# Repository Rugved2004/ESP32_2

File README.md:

# ESP32_2 - KiCad PCB Project

A custom ESP32-based PCB design created with KiCad 8.x.

## Overview

This repository contains the complete KiCad project files for an ESP32 development board. The design includes schematic capture, PCB layout, 3D models, and custom footprints/libraries.

## Project Structure

```
ESP32_2/
├── ESP32_2.kicad_pro      # Project configuration
├── ESP32_2.kicad_sch      # Schematic file
├── ESP32_2.kicad_pcb      # PCB layout file
├── ESP32_2.pdf            # PCB fabrication drawing
├── LIB/                   # Custom symbol libraries
├── Footprint/             # Custom footprint libraries
├── 3D_Modelss/            # 3D STEP models for components
├── ESP32_2-backups/       # Automatic KiCad backups
└── imgs/                  # Project images/screenshots
```

## Features

- **ESP32-WROOM-32** module integration
- Custom power management circuitry
- USB-C interface for programming and power
- GPIO breakout headers
- Custom footprint libraries for specific components
- 3D models for mechanical verification

## Getting Started

### Prerequisites

- [KiCad 8.0+](https://www.kicad.org/download/)

### Opening the Project

1. Clone this repository
2. Open `ESP32_2.kicad_pro` in KiCad
3. The schematic and PCB editors will be available

## Manufacturing

### PCB Fabrication

Gerber files can be generated from the PCB editor:
1. Open `ESP32_2.kicad_pcb`
2. File → Fabrication Outputs → Gerbers (.gbr)
3. Use the default settings for most fabs

### Bill of Materials (BOM)

Generate BOM from the schematic editor:
1. Open `ESP32_2.kicad_sch`
2. Tools → Generate Bill of Materials

## Custom Libraries

This project uses custom libraries located in:
- `LIB/` - Schematic symbols
- `Footprint/` - PCB footprints

These are referenced in the project configuration and should be available when opening the project.

## License

This project is open source. Feel free to use, modify, and distribute.

## Author

**Rugved Bhalekar**
- GitHub: [@Rugved2004](https://github.com/Rugved2004)
- Email: rugvedbhalekar2004@gmail.com

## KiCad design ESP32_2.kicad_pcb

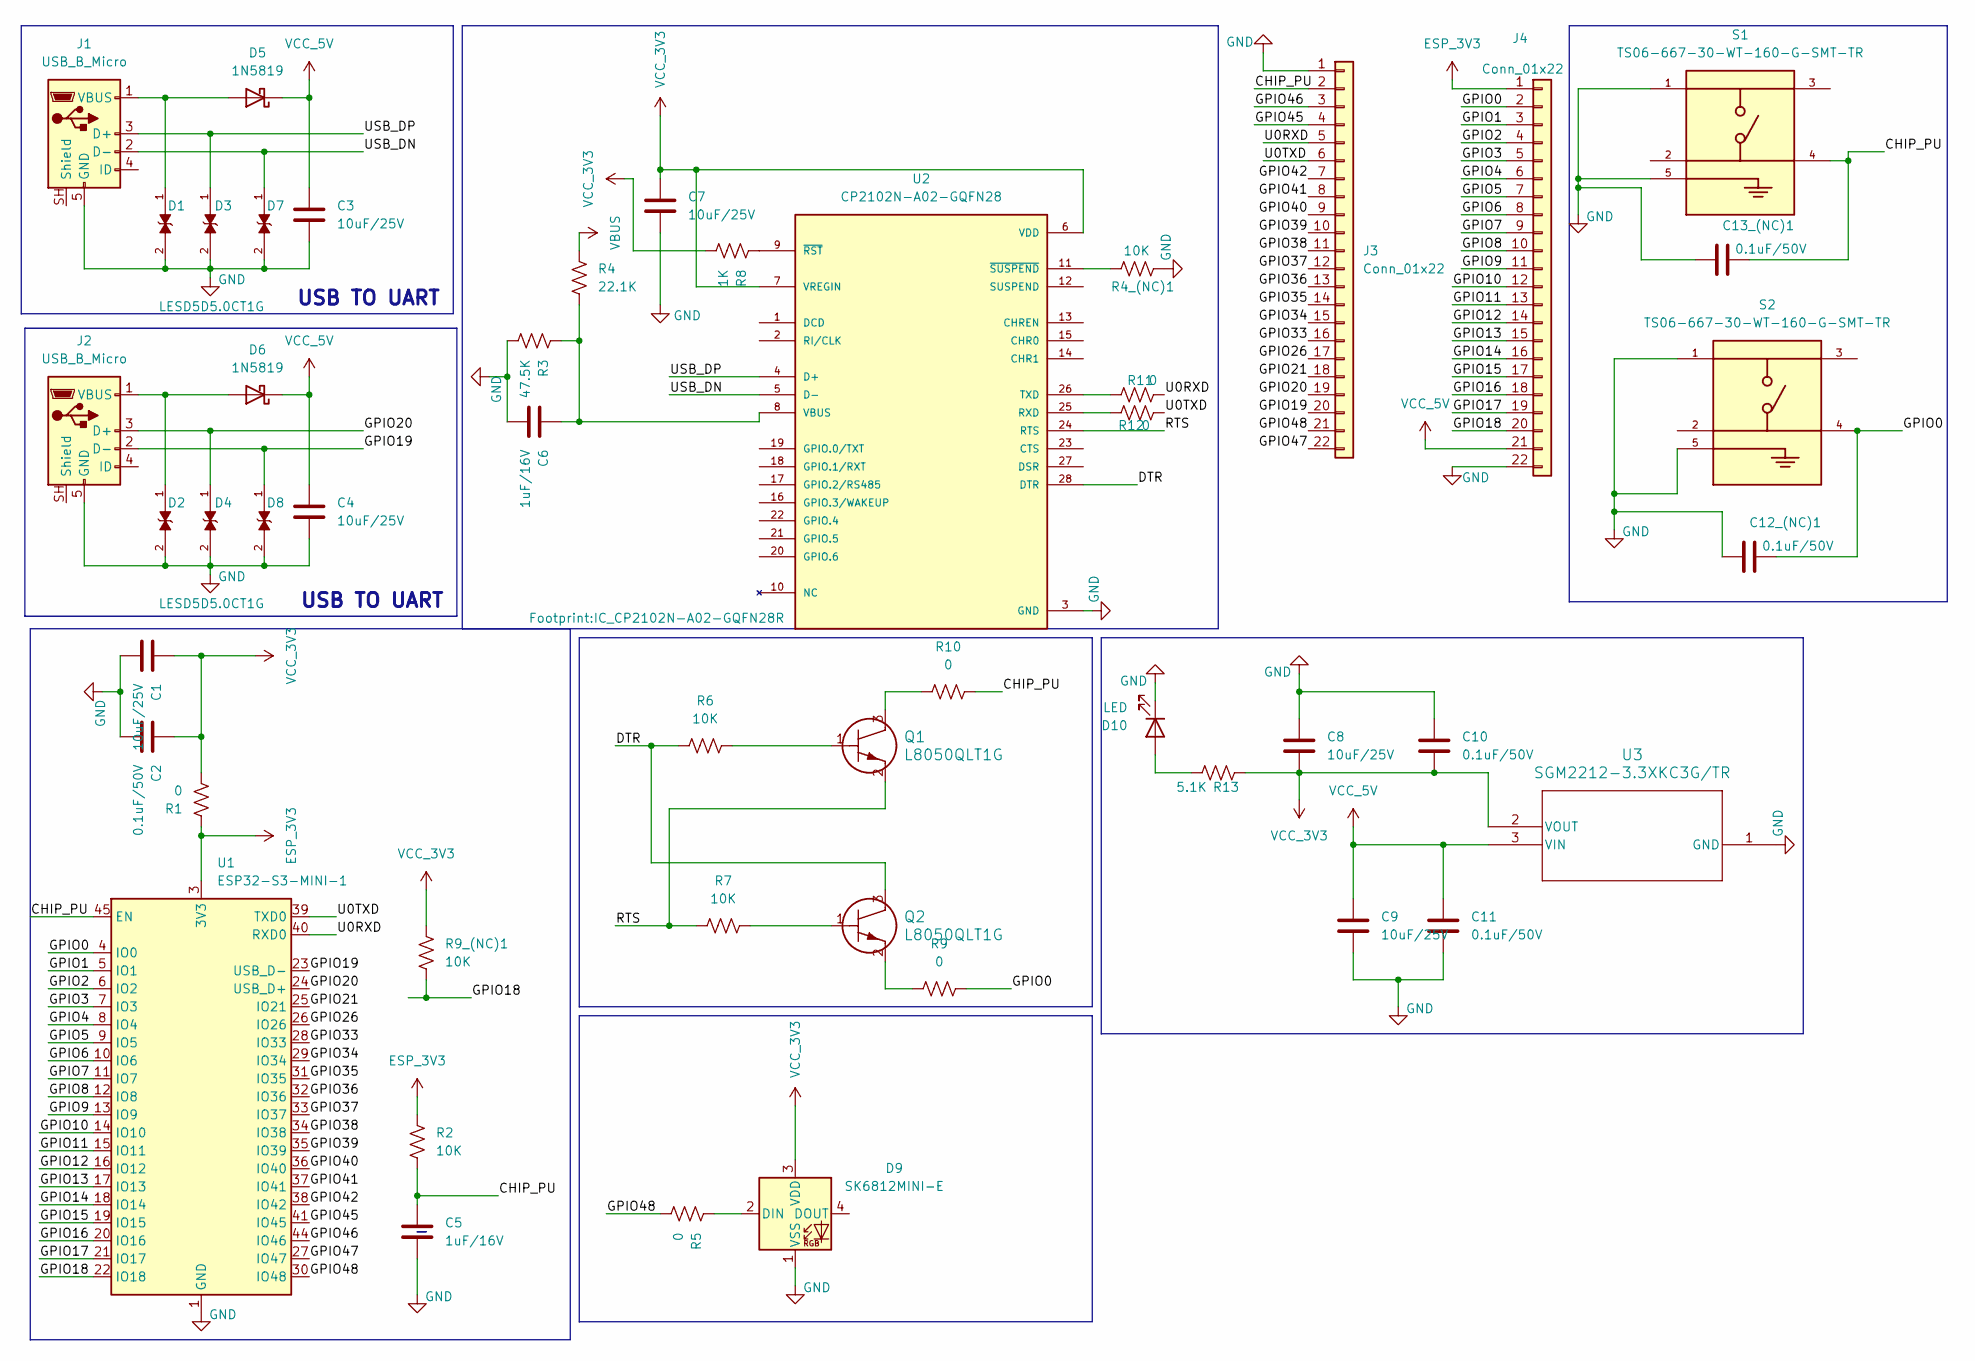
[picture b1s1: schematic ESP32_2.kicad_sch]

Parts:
C1, C3, C4, C7, C8, C9: 10uF/25V; C_0805_2012Metric
C2, C10, C11, C12_(NC)1, C13_(NC)1: 0.1uF/50V; C_0603_1608Metric
C5, C6: 1uF/16V; C_0603_1608Metric
D1, D2, D3, D4, D7, D8: LESD5D5.0CT1G; TVS_LESD5D5.0CT1G; PARTREV O
D5, D6: 1N5819; D_SOD-123
D9: SK6812MINI-E
D10: LED; LED_0603_1608Metric
J1, J2: USB_B_Micro; USB_Micro-B_Molex-105133-0001
J3, J4: Conn_01x22; PinHeader_1x22_P2.54mm_Vertical
Q1, Q2: L8050QLT1G; SOT-23_LRC
R1, R5, R9, R10, R11, R12: 0; R_0603_1608Metric
R2, R4_(NC)1, R6, R7, R9_(NC)1: 10K; R_0603_1608Metric
R3: 47.5K; R_0603_1608Metric
R4: 22.1K; R_0603_1608Metric
R8: 1K; R_0603_1608Metric
R13: 5.1K; R_0603_1608Metric
S1, S2: TS06-667-30-WT-160-G-SMT-TR; SW_TS06-667-30-WT-160-G-SMT-TR; PARTREV 1.0
U1: ESP32-S3-MINI-1; ESP32-S2-MINI-1
U2: CP2102N-A02-GQFN28; IC_CP2102N-A02-GQFN28R; PARTREV 1.5
U3: SGM2212-3.3XKC3G/TR; SOT-223-3_SGM2212_SNC-M

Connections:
/CHIP_PU: C5.1, C13_(NC)1.2, J3.2, R2.1, R10.1, S1.4, U1.45 (EN)
/DTR: Q2.3, R6.2, U2.28 (DTR)
/GPIO0: C12_(NC)1.2, J4.2, R9.1, S2.4, U1.4 (IO0)
/GPIO1: J4.3, U1.5 (IO1)
/GPIO2: J4.4, U1.6 (IO2)
/GPIO3: J4.5, U1.7 (IO3)
/GPIO4: J4.6, U1.8 (IO4)
/GPIO5: J4.7, U1.9 (IO5)
/GPIO6: J4.8, U1.10 (IO6)
/GPIO7: J4.9, U1.11 (IO7)
/GPIO8: J4.10, U1.12 (IO8)
/GPIO9: J4.11, U1.13 (IO9)
/GPIO10: J4.12, U1.14 (IO10)
/GPIO11: J4.13, U1.15 (IO11)
/GPIO12: J4.14, U1.16 (IO12)
/GPIO13: J4.15, U1.17 (IO13)
/GPIO14: J4.16, U1.18 (IO14)
/GPIO15: J4.17, U1.19 (IO15)
/GPIO16: J4.18, U1.20 (IO16)
/GPIO17: J4.19, U1.21 (IO17)
/GPIO18: J4.20, R9_(NC)1.1, U1.22 (IO18)
/GPIO19: D8.1, J2.2 (D-), J3.20, U1.23 (USB_D-)
/GPIO20: D4.1, J2.3 (D+), J3.19, U1.24 (USB_D+)
/GPIO21: J3.18, U1.25 (IO21)
/GPIO26: J3.17, U1.26 (IO26)
/GPIO33: J3.16, U1.28 (IO33)
/GPIO34: J3.15, U1.29 (IO34)
/GPIO35: J3.14, U1.31 (IO35)
/GPIO36: J3.13, U1.32 (IO36)
/GPIO37: J3.12, U1.33 (IO37)
/GPIO38: J3.11, U1.34 (IO38)
/GPIO39: J3.10, U1.35 (IO39)
/GPIO40: J3.9, U1.36 (IO40)
/GPIO41: J3.8, U1.37 (IO41)
/GPIO42: J3.7, U1.38 (IO42)
/GPIO45: J3.4, U1.41 (IO45)
/GPIO46: J3.3, U1.44 (IO46)
/GPIO47: J3.22, U1.27 (IO47)
/GPIO48: J3.21, R5.1, U1.30 (IO48)
/RTS: Q1.2, R7.2, U2.24 (RTS)
/U0RXD: J3.5, R11.2, U1.40 (RXD0)
/U0TXD: J3.6, R12.2, U1.39 (TXD0)
/USB_DN: D7.1, J1.2 (D-), U2.5 (D-)
/USB_DP: D3.1, J1.3 (D+), U2.4 (D+)
ESP_3V3: J4.1, R1.2, R2.2, U1.3 (3V3)
GND: C1.2, C2.2, C3.2, C4.2, C5.2, C6.1, C7.2, C8.1, C9.2, C10.1, C11.2, C12_(NC)1.1, C13_(NC)1.1, D1.2, D2.2, D3.2, D4.2, D7.2, D8.2, D9.1 (VSS), D10.1 (K), J1.5 (GND), J2.5 (GND), J3.1, J4.22, R3.1, R4_(NC)1.2, S1.1, S1.5, S2.1, S2.5, U1.1 (GND), U1.2 (GND), U1.42 (GND), U1.43 (GND), U1.46 (GND), U1.47 (GND), U1.48 (GND), U1.49 (GND), U1.50 (GND), U1.51 (GND), U1.52 (GND), U1.53 (GND), U1.54 (GND), U1.55 (GND), U1.56 (GND), U1.57 (GND), U1.58 (GND), U1.59 (GND), U1.60 (GND), U1.61 (GND), U1.62 (GND), U1.63 (GND), U1.64 (GND), U1.65 (GND), U2.3 (GND), U2.29 (GND), U3.1 (GND)
unnamed: D1.1, D5.2 (A), J1.1 (VBUS)
unnamed: D2.1, D6.2 (A), J2.1 (VBUS)
unnamed: D9.2 (DIN), R5.2
unnamed: D10.2 (A), R13.2
unnamed: Q1.1, R6.1
unnamed: Q1.3, R10.2
unnamed: Q2.1, R7.1
unnamed: Q2.2, R9.2
unnamed: R12.1, U2.25 (RXD)
unnamed: R11.1, U2.26 (TXD)
unnamed: C6.2, R3.2, R4.2, U2.8 (VBUS)
unnamed: R8.2, U2.9 (~RST)
unnamed: R4_(NC)1.1, U2.11 (~SUSPEND)
VBUS: R4.1
VCC_3V3: C1.1, C2.1, C7.1, C8.2, C10.2, D9.3 (VDD), R1.1, R8.1, R9_(NC)1.2, R13.1, U2.6 (VDD), U2.7 (VREGIN), U3.2 (VOUT)
VCC_5V: C3.1, C4.1, C9.1, C11.1, D5.1 (K), D6.1 (K), J4.21, U3.3 (VIN)

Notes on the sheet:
USB TO UART

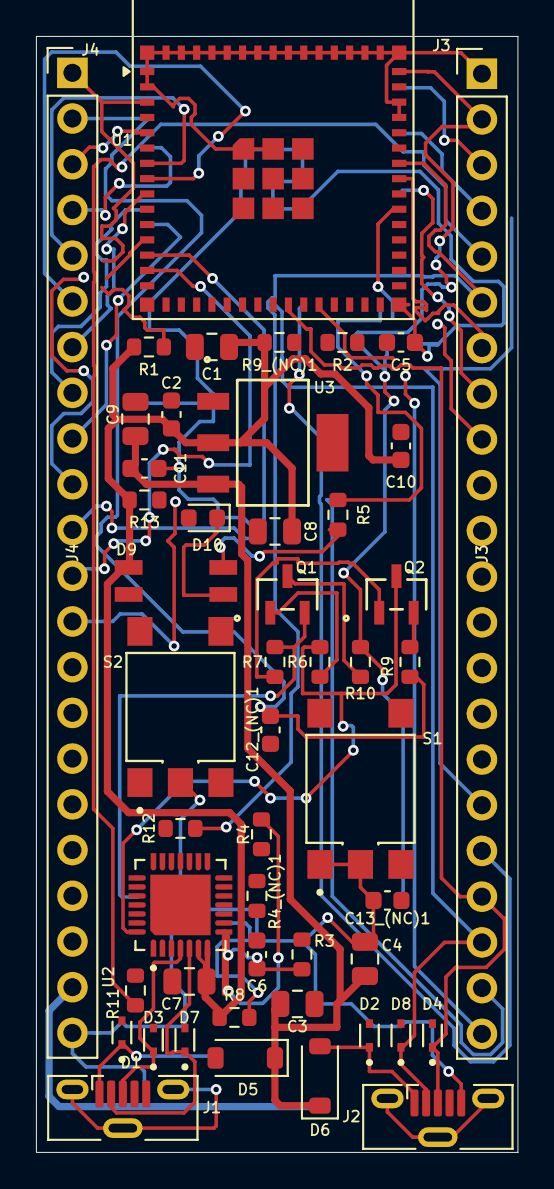
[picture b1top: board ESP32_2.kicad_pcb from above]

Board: 2 copper layers, 26.8 x 62.0 mm, 49 parts (0 on the bottom side), 61 nets.
